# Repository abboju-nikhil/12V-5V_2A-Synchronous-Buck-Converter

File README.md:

# 12 V to 5 V / 2 A Synchronous Buck Converter

A two-layer KiCad design for a synchronous DC-DC converter based on the Texas Instruments LMR33630ADDAR.

## Design targets

| Parameter | Target |
|---|---:|
| Input voltage range | 9–18 V DC |
| Nominal input | 12 V DC |
| Output voltage | 5 V DC |
| Output current | Up to 2 A |
| Switching frequency | 400 kHz |
| Target efficiency | 85% or higher |
| Target output ripple | Below 30 mV peak-to-peak |

Values in this table are design targets, not measured results. No efficiency, ripple, thermal, load-transient, or bench-validation report is included. The project has not been described as industrial-grade or production-qualified.

Review the schematic, layout, component ratings, and manufacturing outputs before fabrication or use. Gerber files are included, but have not been independently checked for manufacturing suitability in this review.

## Project contents

- `12V_5V_2A_Synchronous_Buck_converter.kicad_pro`, `.kicad_sch`, and `.kicad_pcb` — KiCad project, schematic, and board
- `BOM/` — bill of materials
- `Drill Files/` — drill outputs
- `Gerber files/` — board manufacturing layers
- `Layout/` — layer exports and board renders
- `Schematic/` — schematic PDF
- `3D_Image/` and `3D_Models/` — board render and component models
- `Symbol.Kicad_sym/` and `footprints.pretty/` — local KiCad libraries
- `pick and place files/` — component placement data
- `fp-lib-table` — KiCad footprint library table

## Tools

KiCad 10

## License

No license file is included. Do not assume reuse permissions; contact the author for permission.

**Author:** Abboju Nikhil

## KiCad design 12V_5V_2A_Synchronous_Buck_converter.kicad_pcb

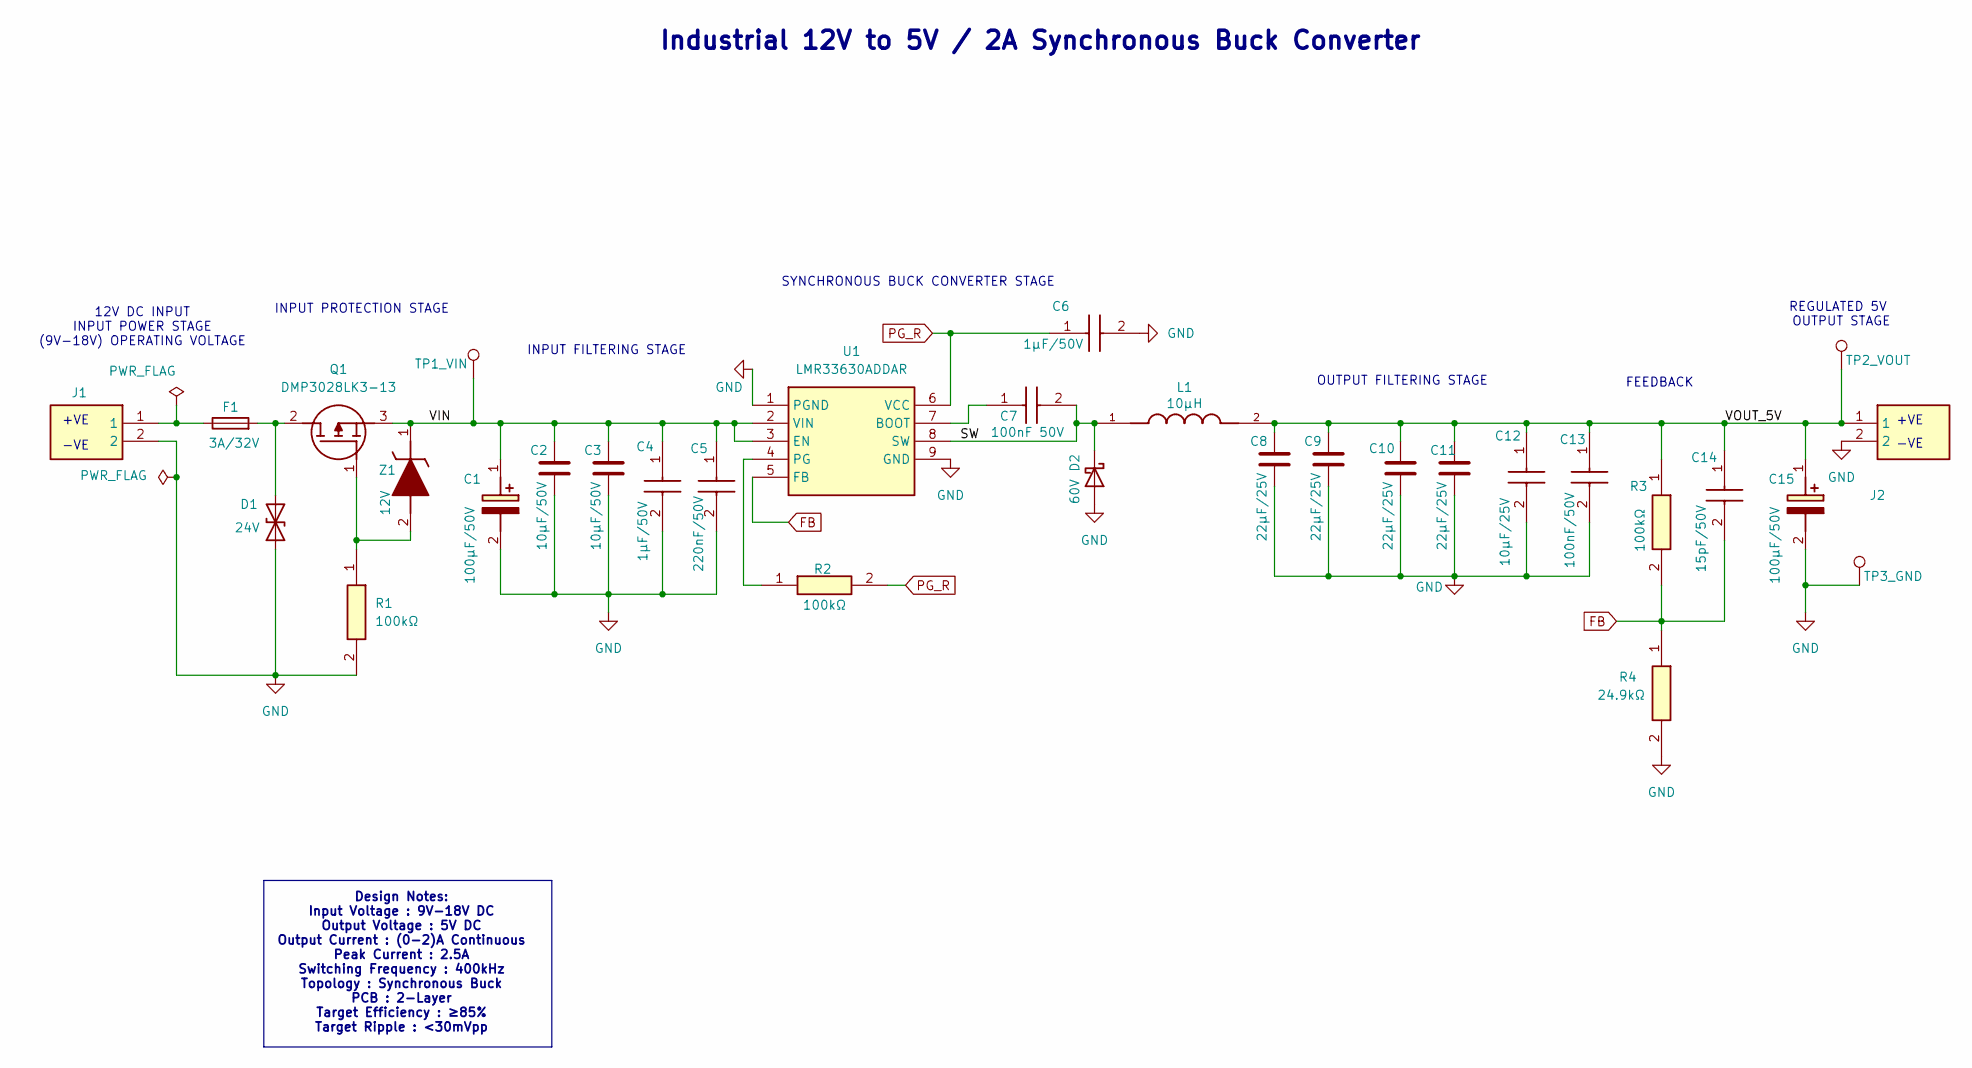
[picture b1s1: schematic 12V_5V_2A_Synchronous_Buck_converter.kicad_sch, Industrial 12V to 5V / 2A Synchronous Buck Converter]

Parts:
C1, C15: 100µF/50V; CAPAE830X1100N; MPN EEE-FK1H101GP
C2, C3: 10µF/50V; c2; MPN CL31B106KBHNNNE
C4: 1µF/50V; CAPC1608X95N; MPN CL10B105KB8NQNC
C5: 220nF/50V; CAPC1608X90N; MPN CL10B224KB8NNNC
C6: 1µF/50V; CAPC1608X95N; MPN CL10B105KB8NQNC; Mouser Part Number 80-C0603C105K3R
C7: 100nF 50V; CAPC1608X90N; MPN CL10B104KB8NNNC
C8, C9, C10, C11: 22µF/25V; CAPC3225X270N; MPN CC1210KKX7R8BB226
C12: 10µF/25V; CAPC2013X113N; MPN 0805X7R106KT1AT
C13: 100nF/50V; CAPC1608X90N; MPN CL10B104KB8NNNC
C14: 15pF/50V; CAPC1608X90N; MPN CL10C150JB8NNNC
D1: 24V; Diode_1; MPN SMBJ24CAQ-13-F
D2: 60V; PMEG6030EP115; MPN PMEG6030EP,115
F1: 3A/32V; FUSC3216X98N; MPN 0407003.WRA
J1, J2: SHDR2W130P0X500_1X2_1000X810X1000P; MPN 1985849
L1: 10µH; IND_XAL7030-103MEB; MPN XAL7030-103MEB
Q1: DMP3028LK3-13; DMP3028LK313; Mouser Part Number 621-DMP3028LK3-13
R1, R2, R3: 100kΩ; RESC1608X50N; MPN CRCW0603100KFKEA
R4: 24.9kΩ; RESC1608X50N; MPN CRCW060324K9FKEA
TP1: TP1_VIN; TestPoint_THTPad_D1.5mm_Drill0.7mm
TP2: TP2_VOUT; TestPoint_THTPad_D1.5mm_Drill0.7mm
TP3: TP3_GND; TestPoint_THTPad_D1.5mm_Drill0.7mm
U1: LMR33630ADDAR; SOIC127P600X170-9N; MPN LMR33630ADDAR
Z1: 12V; SOD3716X145N; MPN MMSZ5242B-7-F

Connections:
/SW: C7.2, D2.1 (K), L1.1, U1.8 (SW)
/VIN: C1.1 (+), C2.1, C3.1, C4.1, C5.1, Q1.3 (S), TP1.1 (1_1), U1.2 (VIN), U1.3 (EN), Z1.1 (K)
/VOUT_5V: C8.1, C9.1, C10.1, C11.1, C12.1, C13.1, C14.1, C15.1 (+), J2.1, L1.2, R3.1, TP2.1 (1_1)
FB: C14.2, R3.2, R4.1, U1.5 (FB)
GND: C1.2 (-), C2.2, C3.2, C4.2, C5.2, C6.2, C8.2, C9.2, C10.2, C11.2, C12.2, C13.2, C15.2 (-), D1.1 (A1), D2.2 (A), J1.2, J2.2, R1.2, R4.2, TP3.1 (1_1), U1.1 (PGND), U1.9 (GND)
unnamed: D1.2 (A2), F1.2, Q1.2 (D)
unnamed: F1.1, J1.1
unnamed: Q1.1 (G), R1.1, Z1.2 (A)
unnamed: C7.1, U1.7 (BOOT)
unnamed: R2.1, U1.4 (PG)
PG_R: C6.1, R2.2, U1.6 (VCC)

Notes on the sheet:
12V DC INPUT INPUT POWER STAGE (9V-18V) OPERATING VOLTAGE
Design Notes: Input Voltage : 9V-18V DC Output Voltage : 5V DC Output Current : (0-2)A Continuous Peak Current : 2.5A Switching Frequency : 400kHz Topology : Synchronous Buck PCB : 2-Layer Target Efficiency : ≥85% Target Ripple : <30mVpp
+VE
-VE
INPUT FILTERING STAGE
Industrial 12V to 5V / 2A Synchronous Buck Converter
SYNCHRONOUS BUCK CONVERTER STAGE
INPUT PROTECTION STAGE
OUTPUT FILTERING STAGE
REGULATED 5V OUTPUT STAGE
FEEDBACK

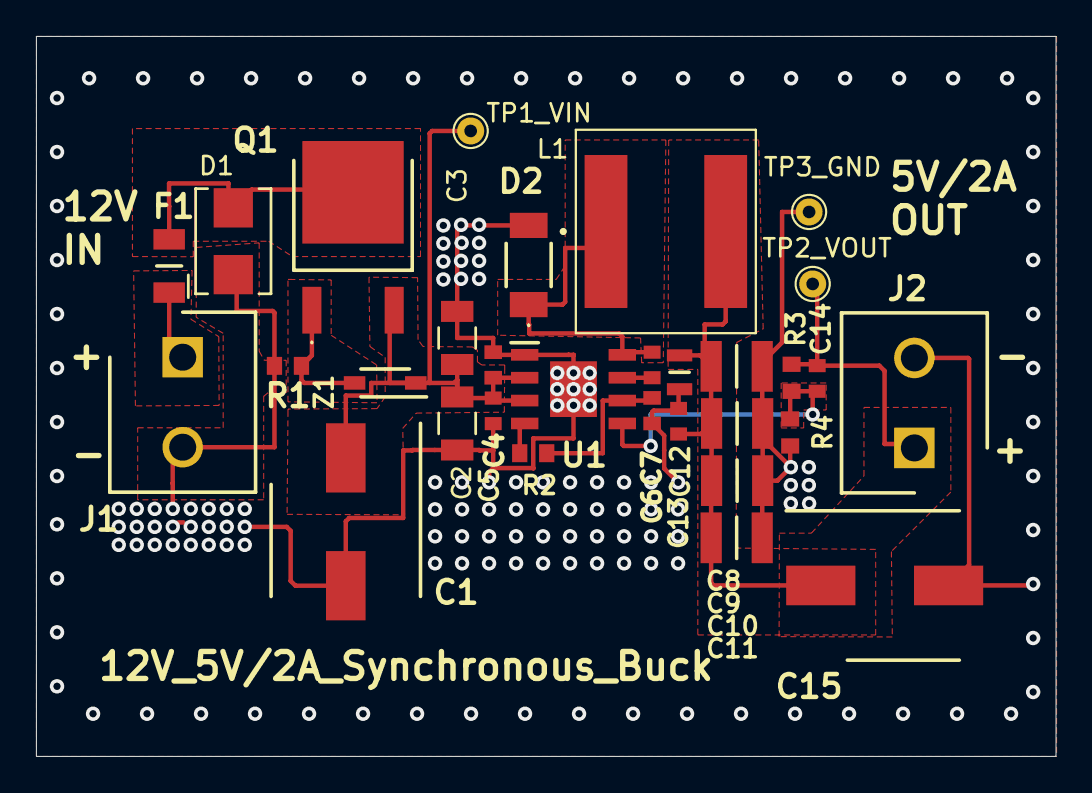
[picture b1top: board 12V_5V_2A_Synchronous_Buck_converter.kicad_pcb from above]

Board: 2 copper layers, 56.6 x 40.0 mm, 31 parts (0 on the bottom side), 11 nets.

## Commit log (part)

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2026-06-29 Add README for 12V to 5V Buck Converter project
    Added detailed project documentation for the 12V to 5V synchronous buck converter, including specifications, features, system architecture, and future improvements.
